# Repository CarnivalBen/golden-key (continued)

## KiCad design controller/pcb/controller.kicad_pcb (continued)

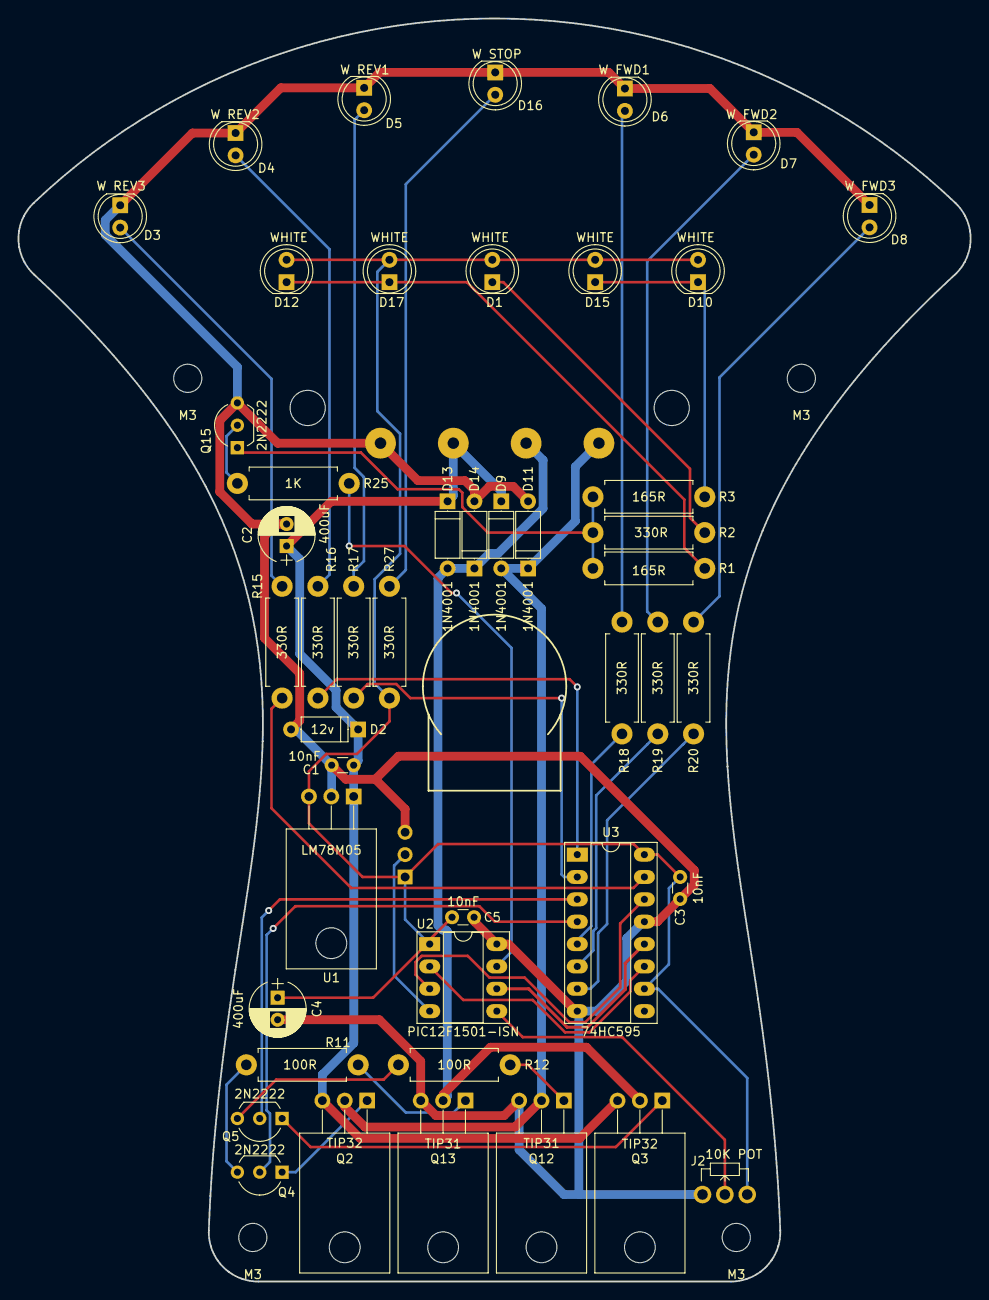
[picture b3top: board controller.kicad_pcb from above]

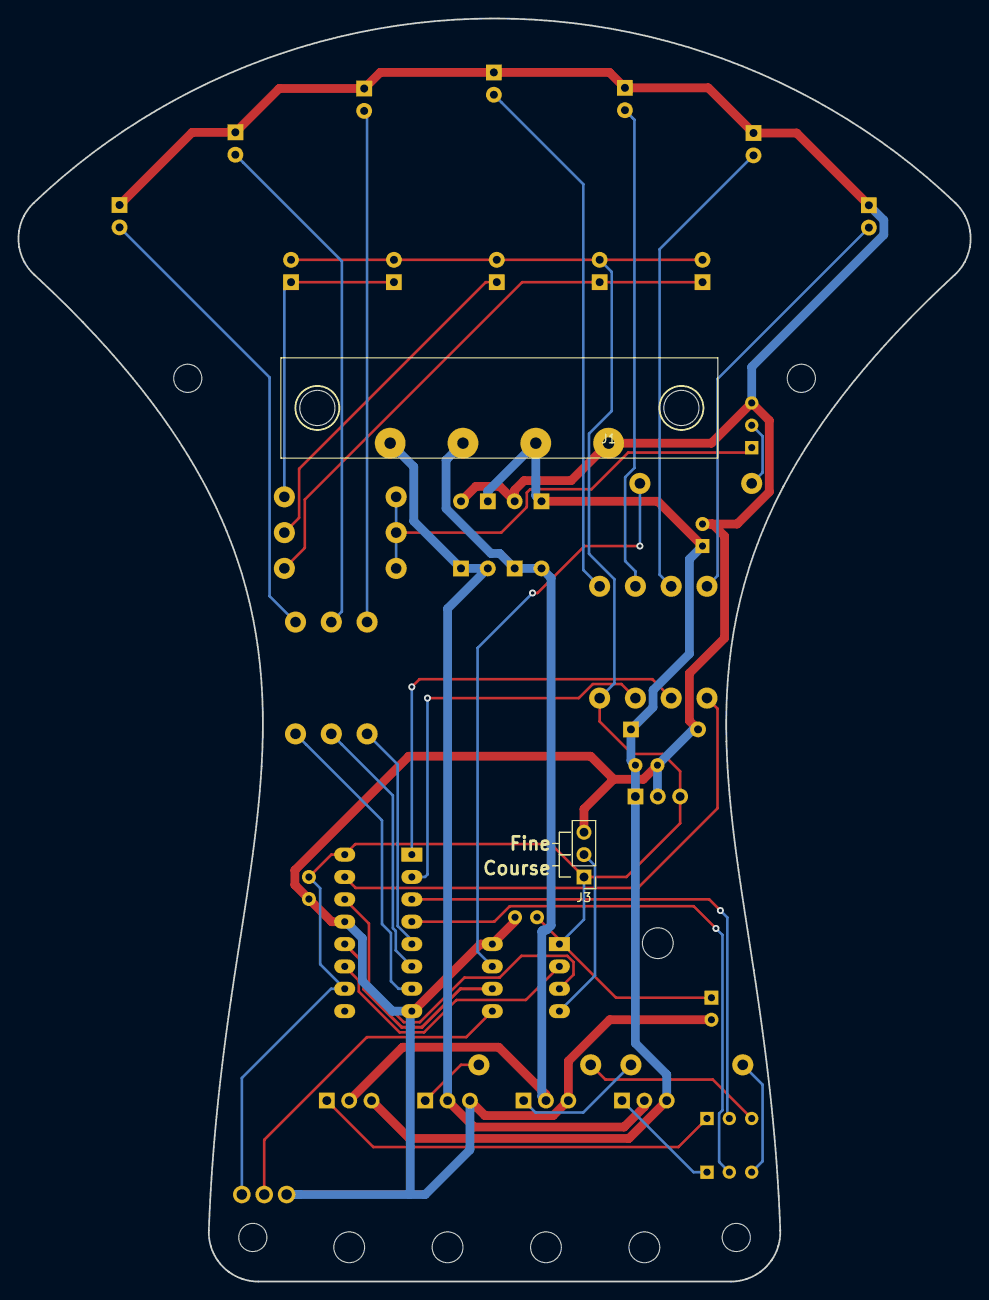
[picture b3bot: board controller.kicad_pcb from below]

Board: 2 copper layers, 108.1 x 143.5 mm, 48 parts (2 on the bottom side), 37 nets.

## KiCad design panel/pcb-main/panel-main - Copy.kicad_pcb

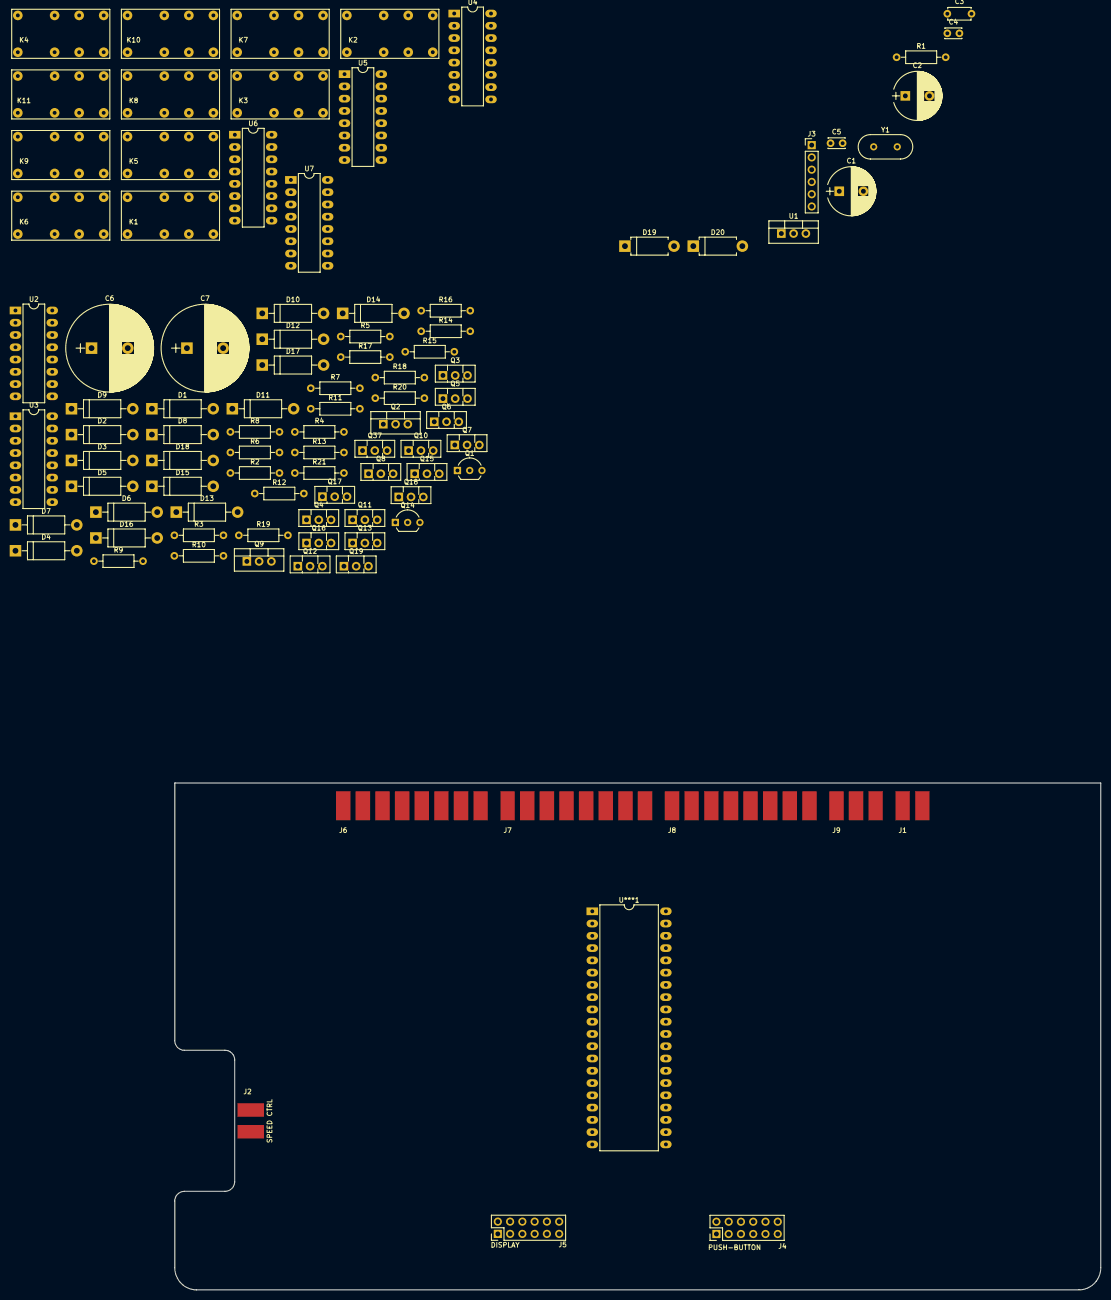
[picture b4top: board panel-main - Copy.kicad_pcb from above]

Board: 2 copper layers, 191.7 x 104.9 mm, 97 parts (0 on the bottom side), 131 nets, no tracks yet.

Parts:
C1, C2: 470uF; CP_Radial_D10.0mm_P5.00mm
C3: 10nF; C_Disc_D4.7mm_W2.5mm_P5.00mm
C4, C5: 33pF; C_Disc_D3.4mm_W2.1mm_P2.50mm
C6, C7: 4700uF; CP_Radial_D18.0mm_P7.50mm
D1, D2, D3, D4, D5, D6, D7, D8, D9, D10, D11, D12, D13, D14, D15, D16, D17, D18: 1N4001; D_DO-15_P12.70mm_Horizontal
D19: 12V; D_DO-15_P10.16mm_Horizontal
D20: 5V; D_DO-15_P10.16mm_Horizontal
J1: PSU IN; Wire_Pads_Edge_1x2
J2: SPEED CTRL; DIN_Socket_Edge_Solder_4pin
J3: ICSP; Pin_Header_Straight_1x06_Pitch2.54mm
J4: PUSH-BUTTON; Pin_Header_Straight_2x06_Pitch2.54mm
J5: DISPLAY; Pin_Header_Straight_2x06_Pitch2.54mm
J6: CONN-L1; Wire_Pads_Edge_2x8
J7: CONN-L2; Wire_Pads_Edge_2x8
J8: CONN-R1; Wire_Pads_Edge_2x8
J9: CONN-R2; Wire_Pads_Edge_2x3
K1, K2, K3, K4, K5, K6, K7, K8, K9, K10, K11: TRK2233-12DC; TRK22X3-XXDC
Q1, Q14: 2N2222; TO-92_Inline_Wide
Q2, Q9: TIP32; TO-220-3_Vertical
Q3, Q4, Q5, Q6, Q7, Q8, Q10, Q11, Q12, Q13, Q15, Q16, Q17, Q18, Q19, Q37: BD679; TO-126_Vertical
R1: 10K; R_Axial_DIN0207_L6.3mm_D2.5mm_P10.16mm_Horizontal
R2, R3, R8, R9: 5K; R_Axial_DIN0207_L6.3mm_D2.5mm_P10.16mm_Horizontal
R4, R5, R6, R7, R10, R11, R12, R13, R14, R15, R16, R17, R18, R19, R20, R21: 1K; R_Axial_DIN0207_L6.3mm_D2.5mm_P10.16mm_Horizontal
U1: LM7805_TO220; TO-220-3_Vertical
U2, U3, U4, U5: 74HC595; DIP-16_W7.62mm_LongPads
U6, U7: ULN2003A; DIP-16_W7.62mm_LongPads
U***1: PIC16F877A; DIP-40_W15.24mm_LongPads
Y1: 20MHz; Crystal_HC49-U_Vertical

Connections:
+5V: C2.1, C3.1, D20.1, J3.2, J5.4, J5.12, J7.13, R1.2, U1.3, U2.10, U2.16, U3.10, U3.16, U4.10, U4.16, U5.10, U5.16, U***1.11, U***1.32
+12V: C1.1, D1.2, D4.2, D19.1, J1.2, J2.4, J5.1, K1.1, K2.1, K3.1, K4.1, K5.1, K6.1, K6.3, K6.6, K7.1, K8.1, K9.1, K9.3, K9.6, K10.1, K11.1, U1.1, U6.9, U7.9
/AUX1-LED: J5.11, U***1.25
/AUX2-LED: J5.10, U***1.26
/Feed Relays/AUX[1]: J7.5, J9.1, K6.4, K6.5
/Feed Relays/AUX[2]: J7.6, J9.2, K9.4, K9.5
/Feed Relays/DATA[IN]: U4.14, U***1.15
/Feed Relays/FEED[A+]: J6.1, J8.1, K1.4
/Feed Relays/FEED[A-]: J6.2, K1.5
/Feed Relays/FEED[B+]: J8.2, K3.4
/Feed Relays/FEED[B-]: J8.3, K3.5
/Feed Relays/FEED[C+]: J6.3, J8.4, K5.4
/Feed Relays/FEED[C-]: J6.4, J8.5, K5.5
/Feed Relays/FEED[D+]: J6.5, K7.4
/Feed Relays/FEED[D-]: J6.6, J8.6, K7.5
/Feed Relays/FEED[E+]: J7.1, K8.4, K8.5
/Feed Relays/FEED[F+]: J7.2, K10.4, K10.5
/Feed Relays/FEED[G+]: J7.3, K11.4, K11.5
/Feed Relays/FEED[H+]: J7.4, K2.4, K2.5
/Feed Relays/FEED[I-]: J8.7, K4.4, K4.5
/HALL[E]: J7.12, U***1.4
/HALL[F]: J7.11, U***1.3
/HALL[G]: J7.10, U***1.2
/PB1: J4.1, U***1.30
/PB2: J4.2, U***1.29
/PB3: J4.3, U***1.28
/PB4: J4.4, U***1.27
/PB5: J4.5, U***1.22
/PB6: J4.12, U***1.21
/PB7: J4.11, U***1.20
/PB8: J4.10, U***1.19
/PB9: J4.9, U***1.8
/PB10: J4.8, U***1.9
/Points Control/DATA[IN]: U2.14, U5.9
/Points Control/DATA[OUT]: J5.2, U3.9
/Points Control/PB1: R4.1, U2.15
/Points Control/PB2: R6.1, U2.1
/Points Control/PB3: R10.1, U2.2
/Points Control/PB4: R12.1, U2.3
/Points Control/PB5: R14.1, U2.4
/Points Control/PB6: R16.1, U2.5
/Points Control/PB7: R18.1, U2.6
/Points Control/PB8: R20.1, U2.7
/Points Control/PF1: R5.1, U3.15
/Points Control/PF2: R7.1, U3.1
/Points Control/PF3: R11.1, U3.2
/Points Control/PF4: R13.1, U3.3
/Points Control/PF5: R15.1, U3.4
/Points Control/PF6: R17.1, U3.5
/Points Control/PF7: R19.1, U3.6
/Points Control/PF8: R21.1, U3.7
/Points Control/POINTS[B1]-COIL: D2.1, J8.16, Q37.3
/Points Control/POINTS[B2]-COIL: D5.1, J8.14, Q4.3
/Points Control/POINTS[B3]-COIL: D7.1, J8.12, Q6.3
/Points Control/POINTS[B4]-COIL: D9.1, J8.10, Q8.3
/Points Control/POINTS[B5]-COIL: D11.1, J6.16, Q11.3
/Points Control/POINTS[B6]-COIL: D13.1, J6.14, Q13.3
/Points Control/POINTS[B7]-COIL: D15.1, J6.12, Q16.3
/Points Control/POINTS[B8]-COIL: D17.1, J6.10, Q18.3
/Points Control/POINTS[F1]-COIL: D3.1, J8.15, Q3.3
/Points Control/POINTS[F2]-COIL: D6.1, J8.13, Q5.3
/Points Control/POINTS[F3]-COIL: D8.1, J8.11, Q7.3
/Points Control/POINTS[F4]-COIL: D10.1, J8.9, Q10.3
/Points Control/POINTS[F5]-COIL: D12.1, J6.15, Q12.3
/Points Control/POINTS[F6]-COIL: D14.1, J6.13, Q15.3
/Points Control/POINTS[F7]-COIL: D16.1, J6.11, Q17.3
/Points Control/POINTS[F8]-COIL: D18.1, J6.9, Q19.3
/Points Control/TANK[1]: R2.2, U***1.33
/Points Control/TANK[2]: R9.2, U***1.34
DCLK: J5.3, U2.11, U3.11, U4.11, U5.11, U***1.16
DLAT: J5.5, U2.12, U3.12, U4.12, U5.12, U***1.17
GND: C1.2, C2.2, C3.2, C4.2, C5.2, C6.2, C7.2, D2.2, D3.2, D5.2, D6.2, D7.2, D8.2, D9.2, D10.2, D11.2, D12.2, D13.2, D14.2, D15.2, D16.2, D17.2, D18.2, D19.2, D20.2, J1.1, J2.1, J3.3, J5.8, J6.7, J6.8, J7.7, J7.8, J7.9, J9.4, J9.5, J9.6, Q1.3, Q14.3, U1.2, U2.8, U2.13, U3.8, U3.13, U4.8, U4.13, U5.8, U5.13, U6.8, U7.8, U***1.12, U***1.31
ICSPCLK: J3.5, U***1.39
ICSPDAT: J3.4, U***1.40
MCLR: J3.1, R1.1, U***1.1
unnamed: C4.1, U***1.13, Y1.1
unnamed: C5.1, U***1.14, Y1.2
unnamed: C6.1, D1.1, Q2.3
unnamed: C7.1, D4.1, Q9.3
unnamed: K1.8, U6.16
unnamed: K2.8, U7.16
unnamed: K3.8, U6.15
unnamed: K4.8, U7.15
unnamed: K5.8, U6.14
unnamed: K6.8, U7.13
unnamed: K7.8, U6.13
unnamed: K8.8, U6.12
unnamed: K9.8, U7.12
unnamed: K10.8, U6.11
unnamed: K11.8, U6.10
unnamed: Q1.1, R3.1
unnamed: Q1.2, R2.1
unnamed: Q2.1, R3.2
unnamed: Q3.1, R5.2
unnamed: Q4.1, R6.2
unnamed: Q5.1, R7.2
unnamed: Q6.1, R10.2
unnamed: Q7.1, R11.2
unnamed: Q8.1, R12.2
unnamed: Q9.1, R8.2
unnamed: Q10.1, R13.2
unnamed: Q11.1, R14.2
unnamed: Q12.1, R15.2
unnamed: Q13.1, R16.2
unnamed: Q14.1, R8.1
unnamed: Q14.2, R9.1
unnamed: Q15.1, R17.2
unnamed: Q16.1, R18.2
unnamed: Q17.1, R19.2
unnamed: Q18.1, R20.2
unnamed: Q19.1, R21.2
unnamed: Q37.1, R4.2
unnamed: U2.9, U3.14
unnamed: U4.1, U6.2
unnamed: U4.2, U6.3
unnamed: U4.3, U6.4
unnamed: U4.4, U6.5
unnamed: U4.5, U6.6
unnamed: U4.6, U6.7
unnamed: U4.7, U7.1
unnamed: U4.9, U5.14
unnamed: U4.15, U6.1
unnamed: U5.1, U7.3
unnamed: U5.2, U7.4
unnamed: U5.3, U7.5
unnamed: U5.4, U7.6
unnamed: U5.5, U7.7
unnamed: U5.15, U7.2
TANK-DUMP: Q2.2, Q3.2, Q4.2, Q5.2, Q6.2, Q7.2, Q8.2, Q9.2, Q10.2, Q11.2, Q12.2, Q13.2, Q15.2, Q16.2, Q17.2, Q18.2, Q19.2, Q37.2
TRACK+: J2.3, K1.3, K2.3, K2.6, K3.3, K5.3, K7.3, K8.3, K8.6, K10.3, K10.6, K11.3, K11.6
TRACK-: J2.2, K1.6, K3.6, K4.3, K4.6, K5.6, K7.6

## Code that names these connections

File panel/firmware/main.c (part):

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    TRISD = 0b11111111;   
    TRISE = 0b00000000;
        
    RB3 = 0;
    RB4 = 0;
    RB5 = 0;
    RC3 = 0;
    
    pushbuttons.status.active = 0;
    pushbuttons.status.lock = 0;
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        if (chrgv < CHARGE_PUMP_MAX - 30) {
            charge = 1;
#ifndef DISABLE_NORMAL_LED_USE
            RB4 = 1;
#endif
        }

        if (chrgv >= CHARGE_PUMP_MAX) {
            charge = 0;
#ifndef DISABLE_NORMAL_LED_USE            
            RB4 = 0;
#endif
        }
        
        if (charge) {                             
             if (RC3) {                    
                 RC3 = 0;
             } else {                    
                 RC3 = 1;
             }

         } else {            
             RC3 = 0;
         }
        
        runningTimer++;
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            runningTimer = 0;
#ifndef DISABLE_NORMAL_LED_USE
            if (RB3 == 0) {
                RB3 = 1;

            } else {
                RB3 = 0;
                
            }           
#endif
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        
    if (getHallSensorStatus(0) && fiddleYardPosition != 3) {
#ifndef DISABLE_NORMAL_LED_USE
        RB5 = 1;
#endif
        fiddleYardPosition = 3;
        shifter.feeds.e = (shifter.feeds.a && isolatedfeeds.e) ? 1 : 0;
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        
    } else if (getHallSensorStatus(1) && fiddleYardPosition != 2) {
#ifndef DISABLE_NORMAL_LED_USE
        RB5 = 1;
#endif
        fiddleYardPosition = 2;
        shifter.feeds.e = 0;
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        
    } else if (getHallSensorStatus(2) && fiddleYardPosition != 1) {
#ifndef DISABLE_NORMAL_LED_USE
        RB5 = 1;
#endif
        fiddleYardPosition = 1;
        shifter.feeds.e = 0;
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    }
    
#ifndef DISABLE_NORMAL_LED_USE
    RB5 = 0;
#endif
}

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    
    if (pushbuttons.status.shortpress) {
#ifndef DISABLE_NORMAL_LED_USE
        RB5 = 1; 
#endif        
        CLRWDT();
        if (pushbuttons.buttons.aux1) {            
            if (shifter.feeds.aux1) {
                shifter.feeds.aux1 = 0;
                RC6 = 0;
            } else {
                shifter.feeds.aux1 = 1;
                RC6 = 1;
            }
            refreshShifter();
            
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        CLRWDT();
        if (pushbuttons.buttons.aux2) {            
            if (shifter.feeds.aux2) {
                shifter.feeds.aux2 = 0; 
                RC7 = 0;
            } else {
                shifter.feeds.aux2 = 1;
                RC7 = 1;
            }
            refreshShifter();
        }
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
        pushbuttons.status.shortpress = 0;
#ifndef DISABLE_NORMAL_LED_USE
        RB5 = 0;
#endif
    }
    
    if (pushbuttons.status.longpress) {
#ifndef DISABLE_NORMAL_LED_USE
        RB5 = 1;
#endif
        CLRWDT();
        
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        
        pushbuttons.status.longpress = 0;
#ifndef DISABLE_NORMAL_LED_USE
        RB5 = 0;
#endif
    }
    
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       
    while (getChargePumpVoltage() < CHARGE_PUMP_MAX) {
#ifndef DISABLE_NORMAL_LED_USE
        RB4 = 1;
#endif
        RC3 = 1;
        _delaywdt(1001);
        RC3 = 0;
        _delaywdt(1001);
    }
#ifndef DISABLE_NORMAL_LED_USE
    RB4 = 0;
#endif
}

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            RC0 = (reg & mask) ? 1 : 0;

            NOP();
            RC1 = 1;
            NOP();
            NOP();
            RC1 = 0;
            NOP();

            mask = mask >> 1;
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        CLRWDT();
    }
    
    RC2 = 1;
    NOP();
    NOP();
    RC2 = 0;
    
}

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
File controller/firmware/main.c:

// CONFIG1
#pragma config FOSC = INTOSC    //  (INTOSC oscillator; I/O function on CLKIN pin)
#pragma config WDTE = OFF        // Watchdog Timer Enable (WDT enabled)
#pragma config PWRTE = OFF      // Power-up Timer Enable (PWRT disabled)
#pragma config MCLRE = OFF      // MCLR Pin Function Select (MCLR/VPP pin function is digital input)
#pragma config CP = OFF         // Flash Program Memory Code Protection (Program memory code protection is disabled)
#pragma config BOREN = ON       // Brown-out Reset Enable (Brown-out Reset enabled)
#pragma config CLKOUTEN = OFF   // Clock Out Enable (CLKOUT function is disabled. I/O or oscillator function on the CLKOUT pin)

// CONFIG2
#pragma config WRT = OFF        // Flash Memory Self-Write Protection (Write protection off)
#pragma config PLLEN = ON       // PLL Enable (4x PLL enabled)
#pragma config STVREN = ON      // Stack Overflow/Underflow Reset Enable (Stack Overflow or Underflow will cause a Reset)
#pragma config BORV = LO        // Brown-out Reset Voltage Selection (Brown-out Reset Voltage (Vbor), low trip point selected.)
#pragma config LPBOREN = OFF    // Low Power Brown-out Reset enable bit (LPBOR is disabled)
#pragma config LVP = OFF         // Low-Voltage Programming Enable (Low-voltage programming enabled)

#include <xc.h>
#include <stdio.h>
#include <stdlib.h>
#include "main.h"

volatile union {
    struct {
        unsigned F3 : 1;
        unsigned F2 : 1;
        unsigned F1 : 1;
        unsigned FWD : 1;
        unsigned REV : 1;
        unsigned R1 : 1;
        unsigned R2 : 1;
        unsigned R3 : 1;
    };
    byte shiftData;
} output;

byte trainDirection;
word pwmCount;

//const byte speedPulse[] = { 0x0,0x0,0x0,0x0,0x0,0x0,0x0,0x0,0x45,0x48,0x4B,0x4D,0x4F,0x51,0x53,0x55,0x57,0x59,0x5B,0x5C,0x5E,0x5F,0x61,0x62,0x64,0x65,0x66,0x67,0x69,0x6A,0x6B,0x6C,0x6D,0x6E,0x6F,0x70,0x71,0x72,0x73,0x74,0x75,0x76,0x77,0x78,0x79,0x7A,0x7A,0x7B,0x7C,0x7D,0x7D,0x7E,0x7F,0x80,0x80,0x81,0x82,0x82,0x83,0x84,0x84,0x85,0x86,0x86,0x87,0x87,0x88,0x89,0x89,0x8A,0x8A,0x8B,0x8B,0x8C,0x8C,0x8D,0x8E,0x8E,0x8F,0x8F,0x90,0x90,0x91,0x91,0x91,0x92,0x92,0x93,0x93,0x94,0x94,0x95,0x95,0x96,0x96,0x96,0x97,0x97,0x98,0x98,0x98,0x99,0x99,0x9A,0x9A,0x9A,0x9B,0x9B,0x9C,0x9C,0x9C,0x9D,0x9D,0x9D,0x9E,0x9E,0x9E,0x9F,0x9F,0x9F,0xA0,0xA0,0xA0,0xA1,0xA1,0xA1,0xA2,0xA2,0xA2,0xA3,0xA3,0xA3,0xA4,0xA4,0xA4,0xA5,0xA5,0xA5,0xA6,0xA6,0xA6,0xA6,0xA7,0xA7,0xA7,0xA8,0xA8,0xA8,0xA8,0xA9,0xA9,0xA9,0xA9,0xAA,0xAA,0xAA,0xAB,0xAB,0xAB,0xAB,0xAC,0xAC,0xAC,0xAC,0xAD,0xAD,0xAD,0xAD,0xAE,0xAE,0xAE,0xAE,0xAF,0xAF,0xAF,0xAF,0xB0,0xB0,0xB0,0xB0,0xB1,0xB1,0xB1,0xB1,0xB1,0xB2,0xB2,0xB2,0xB2,0xB3,0xB3,0xB3,0xB3,0xB3,0xB4,0xB4,0xB4,0xB4,0xB4,0xB5,0xB5,0xB5,0xB5,0xB6,0xB6,0xB6,0xB6,0xB6,0xB7,0xB7,0xB7,0xB7,0xB7,0xB8,0xB8,0xB8,0xB8,0xB8,0xB8,0xB9,0xB9,0xB9,0xB9,0xB9,0xBA,0xBA,0xBA,0xBA,0xBA,0xBB,0xBB,0xBB,0xBB,0xBB,0xBB,0xBC,0xBC,0xBC,0xBC,0xBC,0xBD,0xBD,0xBD,0xBD,0xBD,0xBD,0xBE,0xBE,0xBE,0xBE,0xBE,0xBE,0xBF,0xBF,0xBF,0xBF};

const byte speedPulse[] = { 0x0,0x0,0x0,0x0,0x0,0x0,0x0,0x0,0x45,0x49,0x4C,0x4F,0x52,0x55,0x57,0x59,0x5C,0x5E,0x60,0x62,0x64,0x65,0x67,0x69,0x6A,0x6C,0x6D,0x6F,0x70,0x71,0x73,0x74,0x75,0x76,0x78,0x79,0x7A,0x7B,0x7C,0x7D,0x7E,0x7F,0x80,0x81,0x82,0x83,0x83,0x84,0x85,0x86,0x87,0x88,0x88,0x89,0x8A,0x8B,0x8B,0x8C,0x8D,0x8E,0x8E,0x8F,0x90,0x90,0x91,0x91,0x92,0x93,0x93,0x94,0x95,0x95,0x96,0x96,0x97,0x97,0x98,0x98,0x99,0x99,0x9A,0x9B,0x9B,0x9C,0x9C,0x9D,0x9D,0x9D,0x9E,0x9E,0x9F,0x9F,0xA0,0xA0,0xA1,0xA1,0xA2,0xA2,0xA2,0xA3,0xA3,0xA4,0xA4,0xA5,0xA5,0xA5,0xA6,0xA6,0xA7,0xA7,0xA7,0xA8,0xA8,0xA8,0xA9,0xA9,0xA9,0xAA,0xAA,0xAB,0xAB,0xAB,0xAC,0xAC,0xAC,0xAD};
const word speedGap[] =   { 0x0,0x0,0x0,0x0,0x7CF,0x789,0x746,0x704,0x6C5,0x688,0x64E,0x615,0x5DE,0x5AA,0x577,0x546,0x516,0x4E9,0x4BD,0x492,0x469,0x441,0x41B,0x3F6,0x3D3,0x3B0,0x38F,0x36F,0x350,0x332,0x316,0x2FA,0x2DF,0x2C5,0x2AD,0x295,0x27D,0x267,0x251,0x23D,0x228,0x215,0x202,0x1F0,0x1DF,0x1CE,0x1BE,0x1AE,0x19F,0x190,0x182,0x175,0x168,0x15B,0x14F,0x143,0x138,0x12D,0x122,0x118,0x10E,0x105,0xFC,0xF3,0xEA,0xE2,0xDA,0xD2,0xCB,0xC4,0xBD,0xB6,0xB0,0xAA,0xA4,0x9E,0x98,0x93,0x8E,0x89,0x84,0x7F,0x7B,0x77,0x72,0x6E,0x6A,0x67,0x63,0x60,0x5C,0x59,0x56,0x53,0x50,0x4D,0x4A,0x48,0x45,0x43,0x40,0x3E,0x3C,0x3A,0x38,0x36,0x34,0x32,0x30,0x2F,0x2D,0x2B,0x2A,0x28,0x27,0x25,0x24,0x23,0x22,0x20,0x1F,0x1E,0x1D,0x1C,0x1B,0x1A,0x19,0x18};

word pulse = 0;
word gap = 0;
byte phase = 0;




int main(void) {

    CLRWDT();
    
    // Oscillator
    OSCCON = 0b01111010;
    
    // PORT SETUP
    INLVLA = 0;
    ANSELA = 0;
    //TRISA0 = 0; // STATUS OUT
    //TRISA1 = 0; // LATCH
    //TRISA2 = 1; // SPEED POTENTIOMETER IN
    //TRISA4 = 0; // DATA OUT
    //TRISA5 = 0; // DATA CLK OUT
    TRISA = 0b00001100;
    ODA1 = 0;
    SLRA1 = 0;
    WPUA = 0;
    LATA0 = 0;
    ANSELA = 0b00001100;
    ADCON0 = 0b00001001;
    ADCON1 = 0b01100000;
    ADCON2 = 0b00000000;  
    FVRCON = 0b00110000;
    
    // TIMER0 SETUP    
    OPTION_REG = 0b11011000;
    TMR0 = 0;   
    pwmCount = 0;
    
    // INTERRUPT SETUP
//    IOCAP = 0b00000000;
//    IOCAN = 0b00001000;
//    IOCAF = 0b00001000;
//    IOCIE = 1;
//    TMR0IE = 0;
  
    GIE = 1;
    
   
    while (1) {                        
        
        updateSpeed();
        setShiftReg();              
        
        CLRWDT();
        LATA0 = 1;
    }
}

void __interrupt() isr() {
    
    //if (TMR0IE && TMR0IF) {
        TMR0IF = 0;
        
        pwmCount--;
        
        if (phase == 0 && pwmCount == 0) {
            pwmCount = gap;
            phase = 1;

            output.FWD = 0;
            output.REV = 0;            

        } else if (phase == 1 && pwmCount == 0) {
            pwmCount = pulse;
            phase = 0;

            if (trainDirection) {
                output.REV = 0;
                output.FWD = 1;
            } else {
                output.FWD = 0;
                output.REV = 1;
            }       
                     
        }     
    //}     
               
}


void updateSpeed() {
    
    byte thresMid = 85; //91;
    byte thresTop = 170; //323;

    ADCON1 = 0b01100000;
    ADCON0 = 0b00001011;
    
    while (ADCON0bits.GO_nDONE);
    
    trainDirection = (ADRESH & 0x80) >> 7;    
    byte speed = (ADRES >> 7);        
    
    if (!trainDirection) speed = 255 - speed;         
    
    if (!RA3) {
        speed = speed / 3;
        thresMid = 85 / 3;
        thresTop = 170 / 3;
    }
    
    pulse = (word)speedPulse[speed >> 1];    
    gap = speedGap[speed >> 1];
    
    
    if (pulse == 0 && TMR0IE == 1) {
        TMR0IE = 0;
        output.FWD = 0;
        output.REV = 0;
        
    } else if (pulse != 0 && TMR0IE == 0) {
        pwmCount = pulse;
        phase = 0;
        TMR0IE = 1;
    }
               
    if (!trainDirection) {        
        output.R3 = 0;
        output.R2 = 0;
        output.R1 = 0;
        output.F1 = pulse > 0;
        output.F2 = pulse > 0 && speed > thresMid;
        output.F3 = pulse > 0 && speed > thresTop; 
        
    } else {
        output.F3 = 0;
        output.F2 = 0;
        output.F1 = 0;
        output.R1 = pulse > 0;
        output.R2 = pulse > 0 && speed > thresMid;
        output.R3 = pulse > 0 && speed > thresTop; 
        
    }    
}




void setShiftReg() {
    
    byte buff = output.shiftData;
    byte mask = 0b10000000;

    do {
        
        if (buff & mask) {
            LATA4 = 1;
        } else {
            LATA4 = 0;
        }
        
        NOP();
        LATA5 = 1;
        NOP();        
        LATA5 = 0;        
        
        mask = mask >> 1;
    } while (mask > 0);
    
    LATA1 = 1;
    NOP();
    LATA1 = 0;
    LATA4 = 0;
    LATA5 = 0;
    
}

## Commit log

2020-06-27 Tweaked controller firmware
2020-06-28 Removed firmware build files.
2020-06-28 Added .gitignore. Further work on controller firmware.
2020-06-28 Controller firmware speed tweaks
2020-06-28 Further firmware tweaks.
2020-06-30 Controller firmware updated speed curves. Tweaked controller schematic.
2020-06-30 Fixed controller firmware gap lookups.
2020-06-30 Fixed LED speed indicator bug that was lighting LEDs 2 and 3 in dead zone
2020-07-08 Tweaks to firmware
2020-07-09 Switched overload to ADC in firmware.
2020-07-09 Tweaks
2020-07-15 Added gradient control to PCB.
2020-07-18 PCB Updates and added panel-fw project.
2020-07-18 Removed project config files from .gitignore.
2020-07-18 Initial firmware code for panel
2020-08-10 Main PCB Update - MOSFETS on Points, 3 tanks.
2020-08-14 Completed all PCBs and added gerber files
2020-08-16 Panel firmware button testing
2020-08-16 Panel firmware - coded button push logic
2020-08-17 Completed panel firmware.
2020-08-18 Added panel firmware initialisation
2020-08-19 Fixed charge pump
2020-08-20 panel firmware bug fixes
2020-08-21 Changed EEPROM read/write method
2020-08-21 bug fixes
2020-08-22 Tweaks to speed controller
2020-08-26 Fixed points mosfet bug
2020-08-28 Added .STLs
2020-08-28 Switched controller pulse graph to /128
